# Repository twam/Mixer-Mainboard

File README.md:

Mixer-Mainboard
===

This repository is part of the USB audio mixer project described on https://www.twam.info/general/building-a-custom-usb-audio-mixer.

## License

[![CC BY-SA 4.0][cc-by-sa-shield]][cc-by-sa]

This work is licensed under a [Creative Commons Attribution-NonCommercial-ShareAlike 4.0 International License][cc-by-sa].

[![CC BY-SA 4.0][cc-by-sa-image]][cc-by-sa]

[cc-by-sa]: http://creativecommons.org/licenses/by-nc-sa/4.0/
[cc-by-sa-image]: https://licensebuttons.net/l/by-nc-sa/4.0/88x31.png
[cc-by-sa-shield]: https://img.shields.io/badge/License-CC%20BY--NC--SA%204.0-lightgrey.svg

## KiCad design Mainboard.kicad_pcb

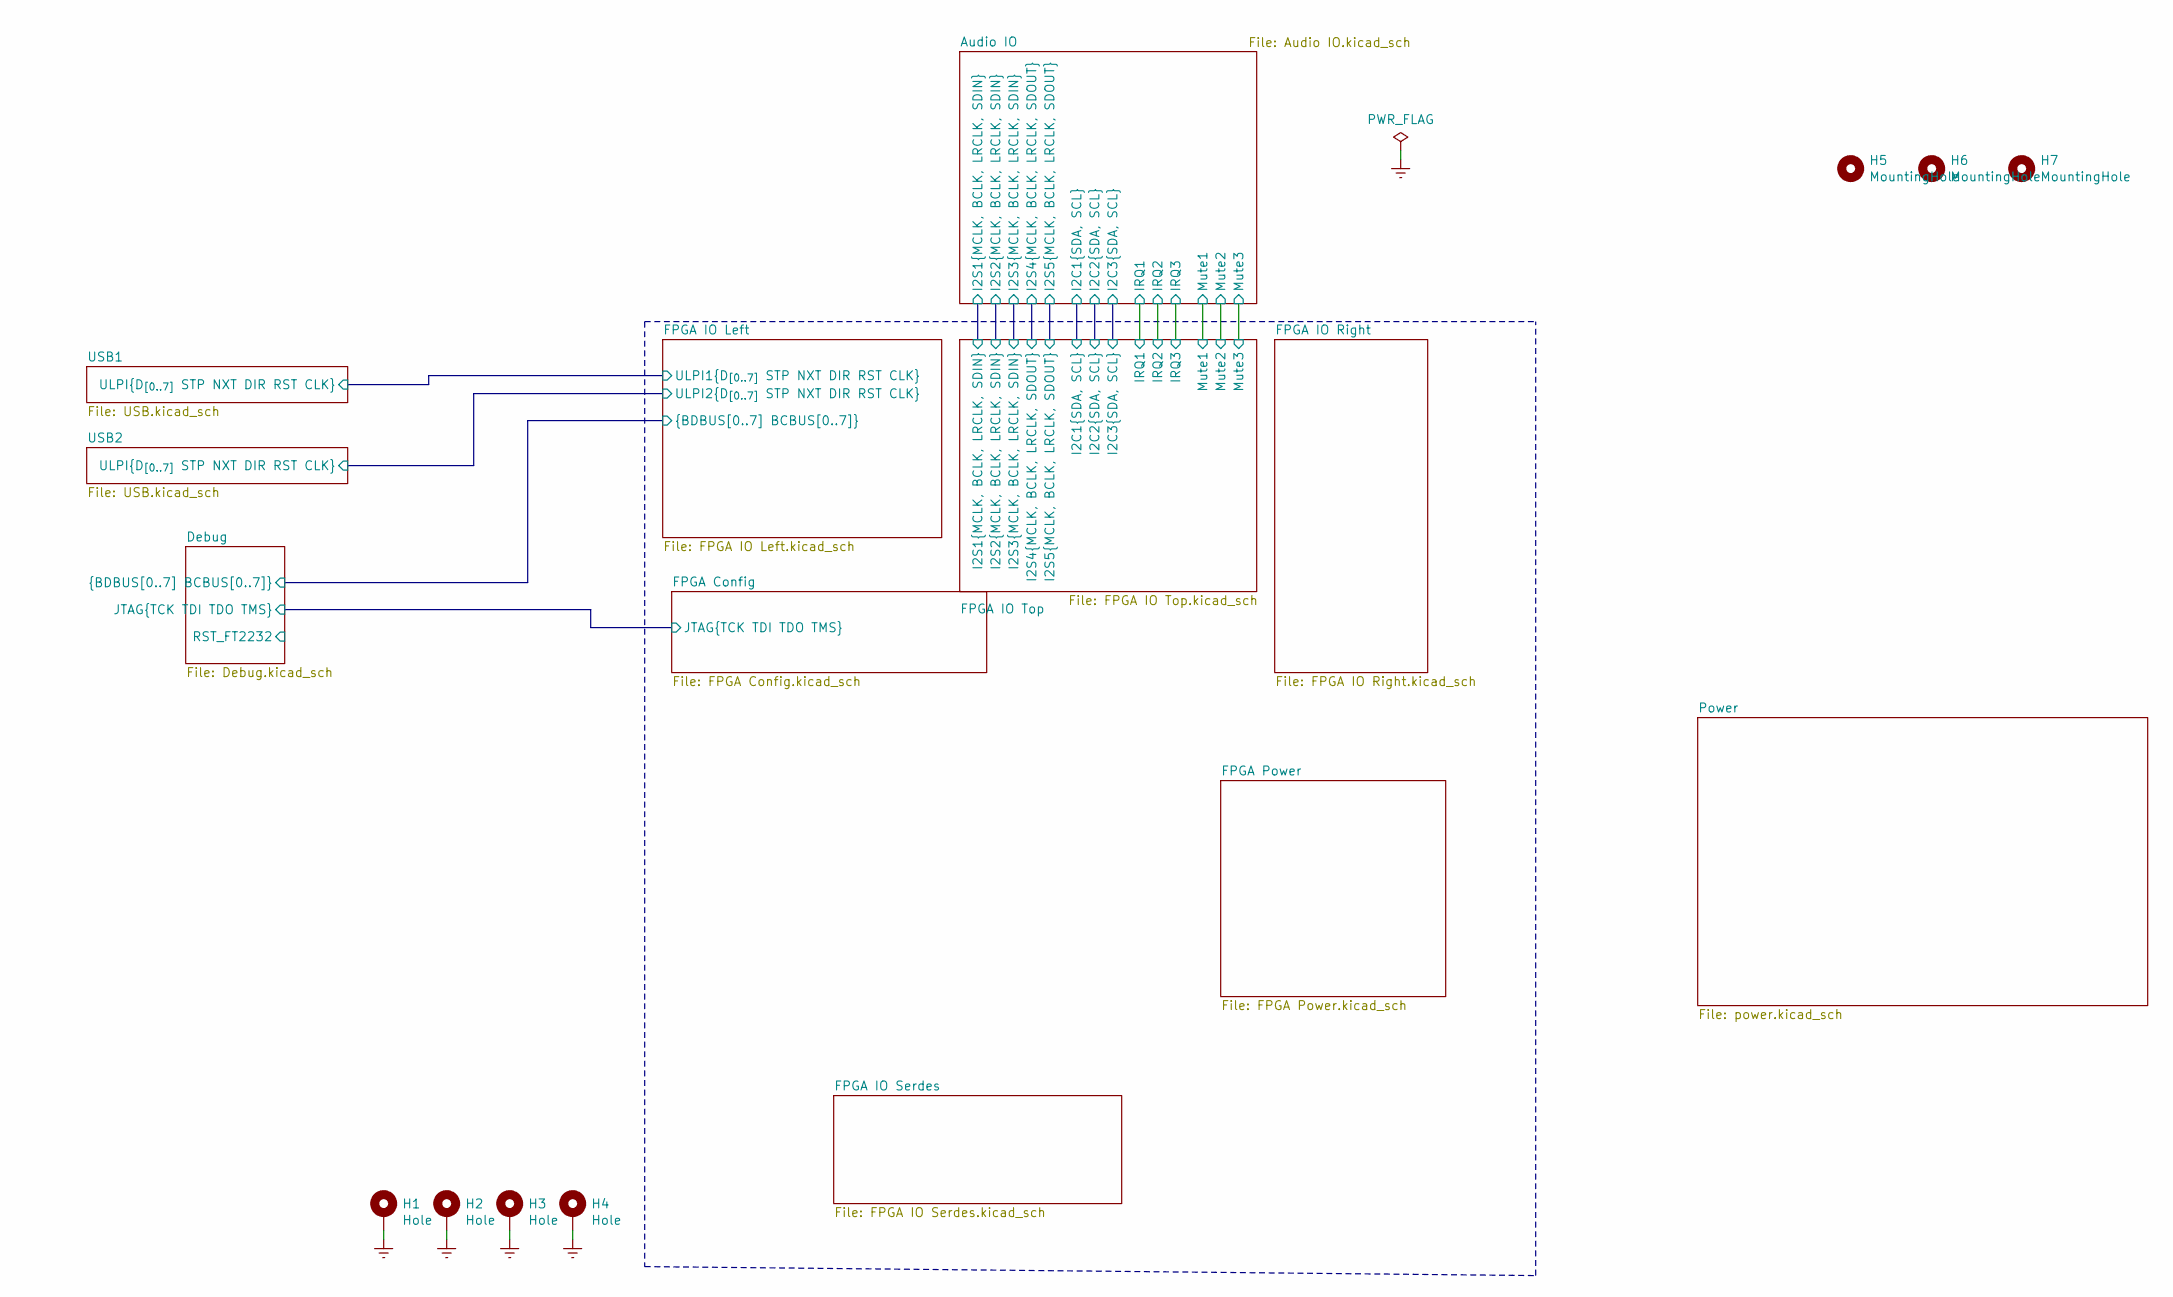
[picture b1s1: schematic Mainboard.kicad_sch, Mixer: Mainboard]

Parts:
H1, H2, H3, H4: Hole; MountingHole_3.2mm_M3_DIN965_Pad
H5, H6, H7: MountingHole; MountingHole_JLCPCB

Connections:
Earth: H1.1, H2.1, H3.1, H4.1; also elsewhere on the board

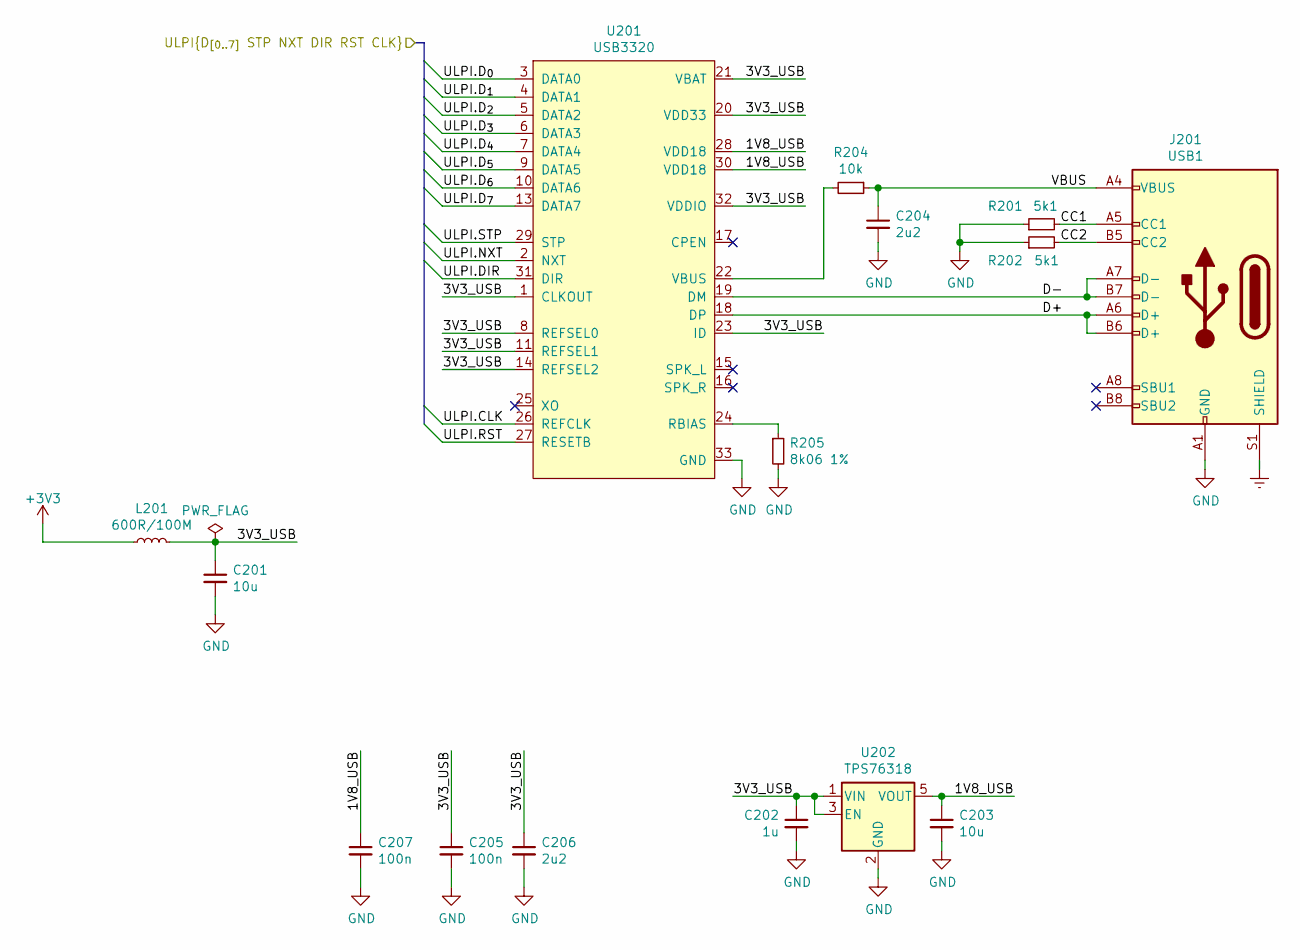
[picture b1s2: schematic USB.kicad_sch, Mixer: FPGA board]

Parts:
C201: 10u; C_0805_2012Metric; LCSC C15850
C202: 1u; C_0603_1608Metric; LCSC C15849
C203: 10u; C_0603_1608Metric; LCSC C19702
C204, C206: 2u2; C_0603_1608Metric; LCSC C23630
C205, C207: 100n; C_0402_1005Metric; LCSC C1525
J201: USB1; USB_C_Receptacle_XKB_TYPE-C-31-M-12; LCSC C165948
L201: 600R/100M; L_0805_2012Metric; LCSC C1017
R201, R202: 5k1; R_0402_1005Metric; LCSC C25905
R204: 10k; R_0402_1005Metric; LCSC C25744
R205: 8k06 1%; R_0603_1608Metric; LCSC C23112
U201: USB3320; QFN-32-1EP_5x5mm_P0.5mm_EP3.3x3.3mm; LCSC C132156
U202: TPS76318; SOT-23-5; LCSC C7099

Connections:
+3V3: L201.1; also elsewhere on the board
/FPGA IO Left/ULPI2.CLK: U201.26 (REFCLK); also elsewhere on the board
/FPGA IO Left/ULPI2.DIR: U201.31 (DIR); also elsewhere on the board
/FPGA IO Left/ULPI2.D_{0}: U201.3 (DATA0); also elsewhere on the board
/FPGA IO Left/ULPI2.D_{1}: U201.4 (DATA1); also elsewhere on the board
/FPGA IO Left/ULPI2.D_{2}: U201.5 (DATA2); also elsewhere on the board
/FPGA IO Left/ULPI2.D_{3}: U201.6 (DATA3); also elsewhere on the board
/FPGA IO Left/ULPI2.D_{4}: U201.7 (DATA4); also elsewhere on the board
/FPGA IO Left/ULPI2.D_{5}: U201.9 (DATA5); also elsewhere on the board
/FPGA IO Left/ULPI2.D_{6}: U201.10 (DATA6); also elsewhere on the board
/FPGA IO Left/ULPI2.D_{7}: U201.13 (DATA7); also elsewhere on the board
/FPGA IO Left/ULPI2.NXT: U201.2 (NXT); also elsewhere on the board
/FPGA IO Left/ULPI2.RST: U201.27 (RESETB); also elsewhere on the board
/FPGA IO Left/ULPI2.STP: U201.29 (STP); also elsewhere on the board
/USB2/1V8_USB: C203.1, C207.1, U201.28 (VDD18), U201.30 (VDD18), U202.5 (VOUT)
/USB2/3V3_USB: C201.1, C202.1, C205.1, C206.1, L201.2, U201.1 (CLKOUT), U201.8 (REFSEL0), U201.11 (REFSEL1), U201.14 (REFSEL2), U201.20 (VDD33), U201.21 (VBAT), U201.23 (ID), U201.32 (VDDIO), U202.1 (VIN), U202.3 (EN)
/USB2/CC1: J201.A5 (CC1), R201.2
/USB2/CC2: J201.B5 (CC2), R202.2
/USB2/D+: J201.A6 (D+), J201.B6 (D+), U201.18 (DP)
/USB2/D-: J201.A7 (D-), J201.B7 (D-), U201.19 (DM)
/USB2/VBUS: C204.1, J201.A4 (VBUS), J201.A9 (VBUS), J201.B4 (VBUS), J201.B9 (VBUS), R204.1
Earth: J201.S1 (SHIELD); also elsewhere on the board
GND: C201.2, C202.2, C203.2, C204.2, C205.2, C206.2, C207.2, J201.A1 (GND), J201.A12 (GND), J201.B1 (GND), J201.B12 (GND), R201.1, R202.1, R205.2, U201.33 (GND), U202.2 (GND); also elsewhere on the board
unnamed: R204.2, U201.22 (VBUS)
unnamed: R205.1, U201.24 (RBIAS)

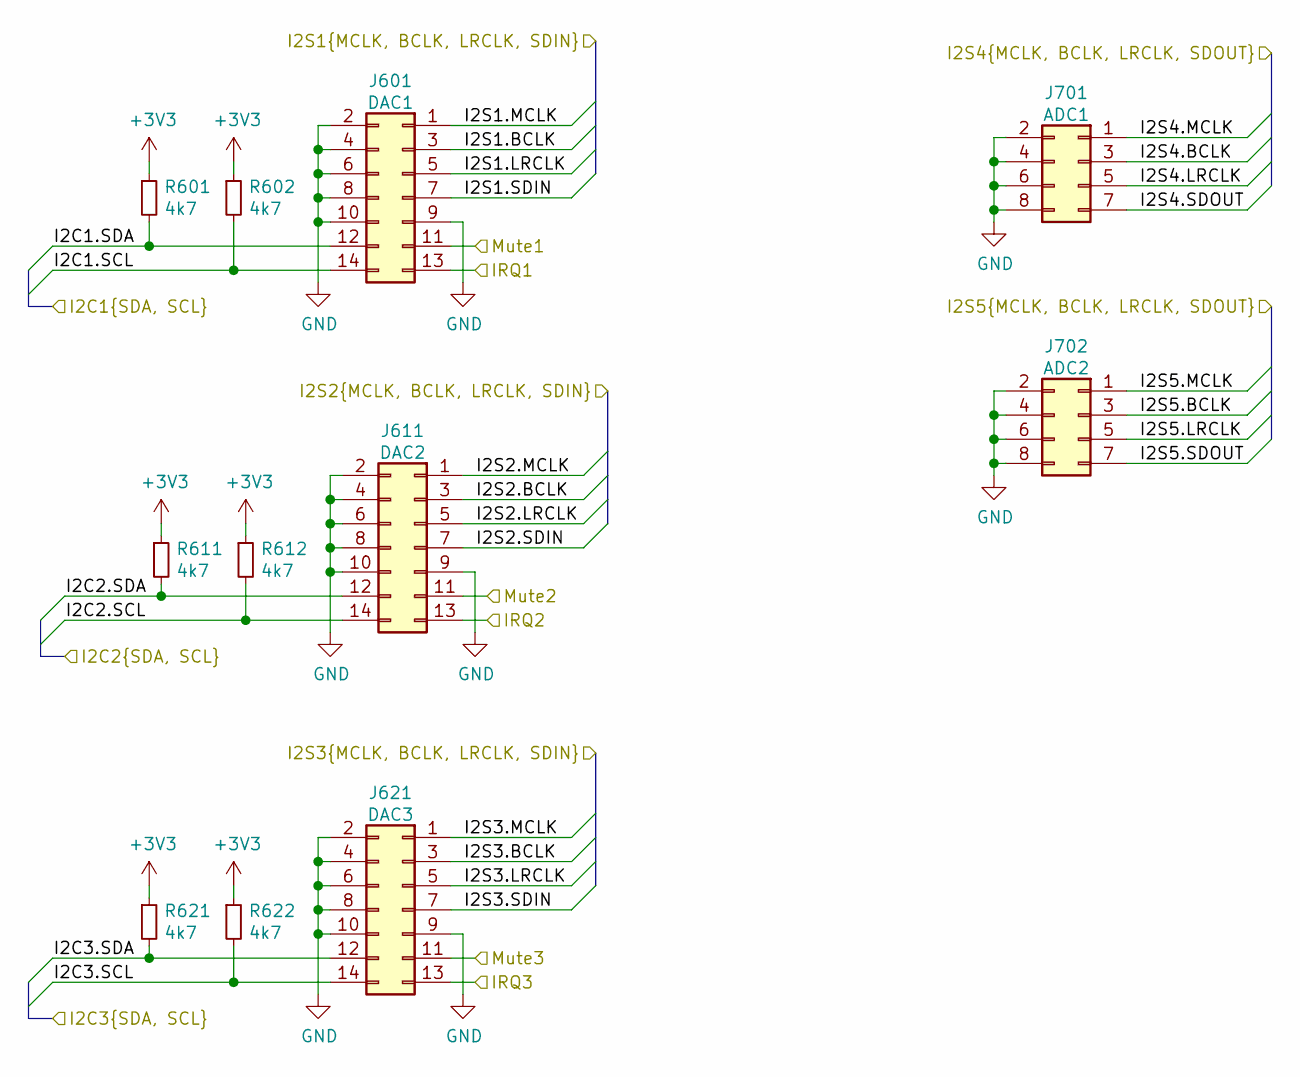
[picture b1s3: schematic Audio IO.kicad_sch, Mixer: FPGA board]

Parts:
J601: DAC1; PinHeader_2x07_P2.54mm_Vertical
J611: DAC2; PinHeader_2x07_P2.54mm_Vertical
J621: DAC3; PinHeader_2x07_P2.54mm_Vertical
J701: ADC1; PinHeader_2x04_P2.54mm_Vertical
J702: ADC2; PinHeader_2x04_P2.54mm_Vertical
R601, R602, R611, R612, R621, R622: 4k7; R_0402_1005Metric; LCSC C25900

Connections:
+3V3: R601.1, R602.1, R611.1, R612.1, R621.1, R622.1; also elsewhere on the board
/Audio IO/I2C1.SCL: J601.14, R602.2; also elsewhere on the board
/Audio IO/I2C1.SDA: J601.12, R601.2; also elsewhere on the board
/Audio IO/I2C2.SCL: J611.14, R612.2; also elsewhere on the board
/Audio IO/I2C2.SDA: J611.12, R611.2; also elsewhere on the board
/Audio IO/I2C3.SCL: J621.14, R622.2; also elsewhere on the board
/Audio IO/I2C3.SDA: J621.12, R621.2; also elsewhere on the board
/Audio IO/I2S1.BCLK: J601.3; also elsewhere on the board
/Audio IO/I2S1.LRCLK: J601.5; also elsewhere on the board
/Audio IO/I2S1.MCLK: J601.1; also elsewhere on the board
/Audio IO/I2S1.SDIN: J601.7; also elsewhere on the board
/Audio IO/I2S2.BCLK: J611.3; also elsewhere on the board
/Audio IO/I2S2.LRCLK: J611.5; also elsewhere on the board
/Audio IO/I2S2.MCLK: J611.1; also elsewhere on the board
/Audio IO/I2S2.SDIN: J611.7; also elsewhere on the board
/Audio IO/I2S3.BCLK: J621.3; also elsewhere on the board
/Audio IO/I2S3.LRCLK: J621.5; also elsewhere on the board
/Audio IO/I2S3.MCLK: J621.1; also elsewhere on the board
/Audio IO/I2S3.SDIN: J621.7; also elsewhere on the board
/Audio IO/I2S4.BCLK: J701.3; also elsewhere on the board
/Audio IO/I2S4.LRCLK: J701.5; also elsewhere on the board
/Audio IO/I2S4.MCLK: J701.1; also elsewhere on the board
/Audio IO/I2S4.SDOUT: J701.7; also elsewhere on the board
/Audio IO/I2S5.BCLK: J702.3; also elsewhere on the board
/Audio IO/I2S5.LRCLK: J702.5; also elsewhere on the board
/Audio IO/I2S5.MCLK: J702.1; also elsewhere on the board
/Audio IO/I2S5.SDOUT: J702.7; also elsewhere on the board
/Audio IO/IRQ1: J601.13; also elsewhere on the board
/Audio IO/IRQ2: J611.13; also elsewhere on the board
/Audio IO/IRQ3: J621.13; also elsewhere on the board
/Audio IO/Mute1: J601.11; also elsewhere on the board
/Audio IO/Mute2: J611.11; also elsewhere on the board
/Audio IO/Mute3: J621.11; also elsewhere on the board
GND: J601.2, J601.4, J601.6, J601.8, J601.9, J601.10, J611.2, J611.4, J611.6, J611.8, J611.9, J611.10, J621.2, J621.4, J621.6, J621.8, J621.9, J621.10, J701.2, J701.4, J701.6, J701.8, J702.2, J702.4, J702.6, J702.8; also elsewhere on the board

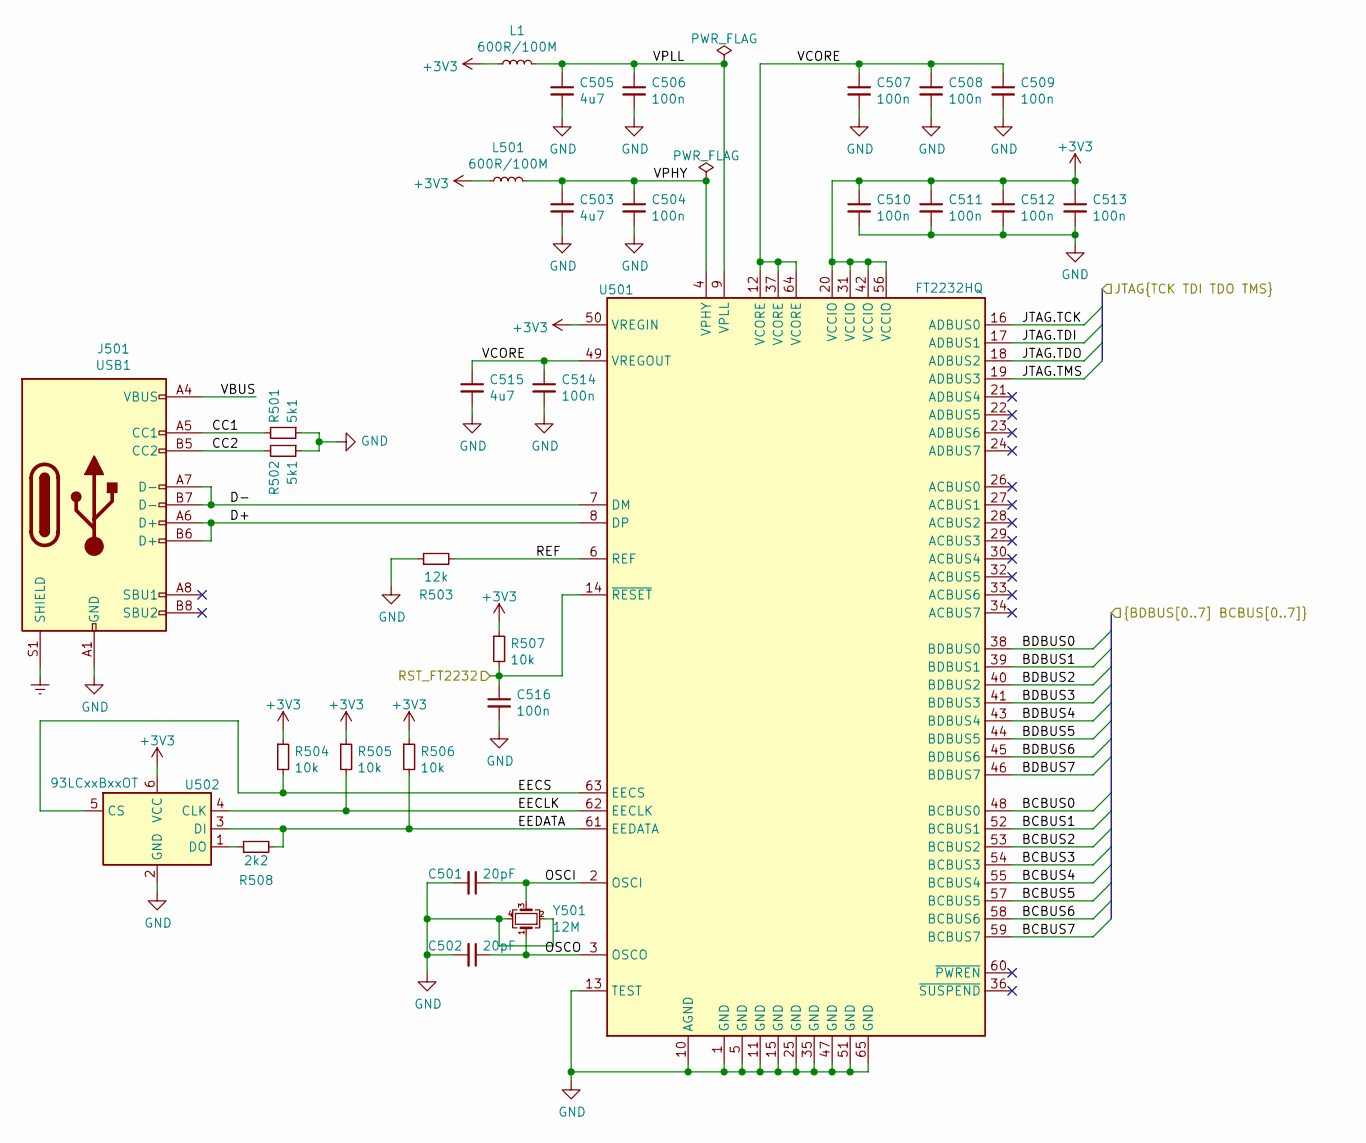
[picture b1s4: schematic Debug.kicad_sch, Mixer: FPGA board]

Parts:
C501, C502: 20pF; C_0402_1005Metric; LCSC C1554
C503, C505, C515: 4u7; C_0603_1608Metric; LCSC C19666
C504, C506, C507, C508, C509, C510, C511, C512, C513, C514, C516: 100n; C_0402_1005Metric; LCSC C1525
J501: USB1; USB_C_Receptacle_XKB_TYPE-C-31-M-12; LCSC C165948
L1, L501: 600R/100M; L_0805_2012Metric; LCSC C1017
R501, R502: 5k1; R_0402_1005Metric; LCSC C25905
R503: 12k; R_0402_1005Metric; LCSC C25752
R504, R505, R506, R507: 10k; R_0402_1005Metric; LCSC C25744
R508: 2k2; R_0402_1005Metric; LCSC C25879
U501: FT2232HQ; QFN-64-1EP_9x9mm_P0.5mm_EP4.35x4.35mm; LCSC C193662
U502: 93LCxxBxxOT; SOT-23-6; LCSC C190271
Y501: 12M; Crystal_SMD_3225-4Pin_3.2x2.5mm; LCSC C9002

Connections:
+3V3: C510.1, C511.1, C512.1, C513.1, L1.1, L501.1, R504.1, R505.1, R506.1, R507.2, U501.20 (VCCIO), U501.31 (VCCIO), U501.42 (VCCIO), U501.50 (VREGIN), U501.56 (VCCIO), U502.6 (VCC); also elsewhere on the board
/Debug/BCBUS0: U501.48 (BCBUS0); also elsewhere on the board
/Debug/BCBUS1: U501.52 (BCBUS1); also elsewhere on the board
/Debug/BCBUS2: U501.53 (BCBUS2); also elsewhere on the board
/Debug/BCBUS3: U501.54 (BCBUS3); also elsewhere on the board
/Debug/BCBUS4: U501.55 (BCBUS4); also elsewhere on the board
/Debug/BCBUS5: U501.57 (BCBUS5); also elsewhere on the board
/Debug/BCBUS6: U501.58 (BCBUS6); also elsewhere on the board
/Debug/BCBUS7: U501.59 (BCBUS7); also elsewhere on the board
/Debug/BDBUS0: U501.38 (BDBUS0); also elsewhere on the board
/Debug/BDBUS1: U501.39 (BDBUS1); also elsewhere on the board
/Debug/BDBUS2: U501.40 (BDBUS2); also elsewhere on the board
/Debug/BDBUS3: U501.41 (BDBUS3); also elsewhere on the board
/Debug/BDBUS4: U501.43 (BDBUS4); also elsewhere on the board
/Debug/BDBUS5: U501.44 (BDBUS5); also elsewhere on the board
/Debug/BDBUS6: U501.45 (BDBUS6); also elsewhere on the board
/Debug/BDBUS7: U501.46 (BDBUS7); also elsewhere on the board
/Debug/CC1: J501.A5 (CC1), R501.2
/Debug/CC2: J501.B5 (CC2), R502.2
/Debug/D+: J501.A6 (D+), J501.B6 (D+), U501.8 (DP)
/Debug/D-: J501.A7 (D-), J501.B7 (D-), U501.7 (DM)
/Debug/EECLK: R505.2, U501.62 (EECLK), U502.4 (CLK)
/Debug/EECS: R504.2, U501.63 (EECS), U502.5 (CS)
/Debug/EEDATA: R506.2, R508.2, U501.61 (EEDATA), U502.3 (DI)
/Debug/JTAG.TCK: U501.16 (ADBUS0); also elsewhere on the board
/Debug/JTAG.TDI: U501.17 (ADBUS1); also elsewhere on the board
/Debug/JTAG.TDO: U501.18 (ADBUS2); also elsewhere on the board
/Debug/JTAG.TMS: U501.19 (ADBUS3); also elsewhere on the board
/Debug/OSCI: C501.1, U501.2 (OSCI), Y501.3
/Debug/OSCO: C502.1, U501.3 (OSCO), Y501.1
/Debug/REF: R503.2, U501.6 (REF)
/Debug/RST_FT2232: C516.1, R507.1, U501.14 (~RESET)
/Debug/VBUS: J501.A4 (VBUS), J501.A9 (VBUS), J501.B4 (VBUS), J501.B9 (VBUS)
/Debug/VCORE: C507.1, C508.1, C509.1, C514.1, C515.1, U501.12 (VCORE), U501.37 (VCORE), U501.49 (VREGOUT), U501.64 (VCORE)
/Debug/VPHY: C503.1, C504.1, L501.2, U501.4 (VPHY)
/Debug/VPLL: C505.1, C506.1, L1.2, U501.9 (VPLL)
Earth: J501.S1 (SHIELD); also elsewhere on the board
GND: C501.2, C502.2, C503.2, C504.2, C505.2, C506.2, C507.2, C508.2, C509.2, C510.2, C511.2, C512.2, C513.2, C514.2, C515.2, C516.2, J501.A1 (GND), J501.A12 (GND), J501.B1 (GND), J501.B12 (GND), R501.1, R502.1, R503.1, U501.1 (GND), U501.5 (GND), U501.10 (AGND), U501.11 (GND), U501.13 (TEST), U501.15 (GND), U501.25 (GND), U501.35 (GND), U501.47 (GND), U501.51 (GND), U501.65 (GND), U502.2 (GND), Y501.2, Y501.4; also elsewhere on the board
unnamed: R508.1, U502.1 (DO)

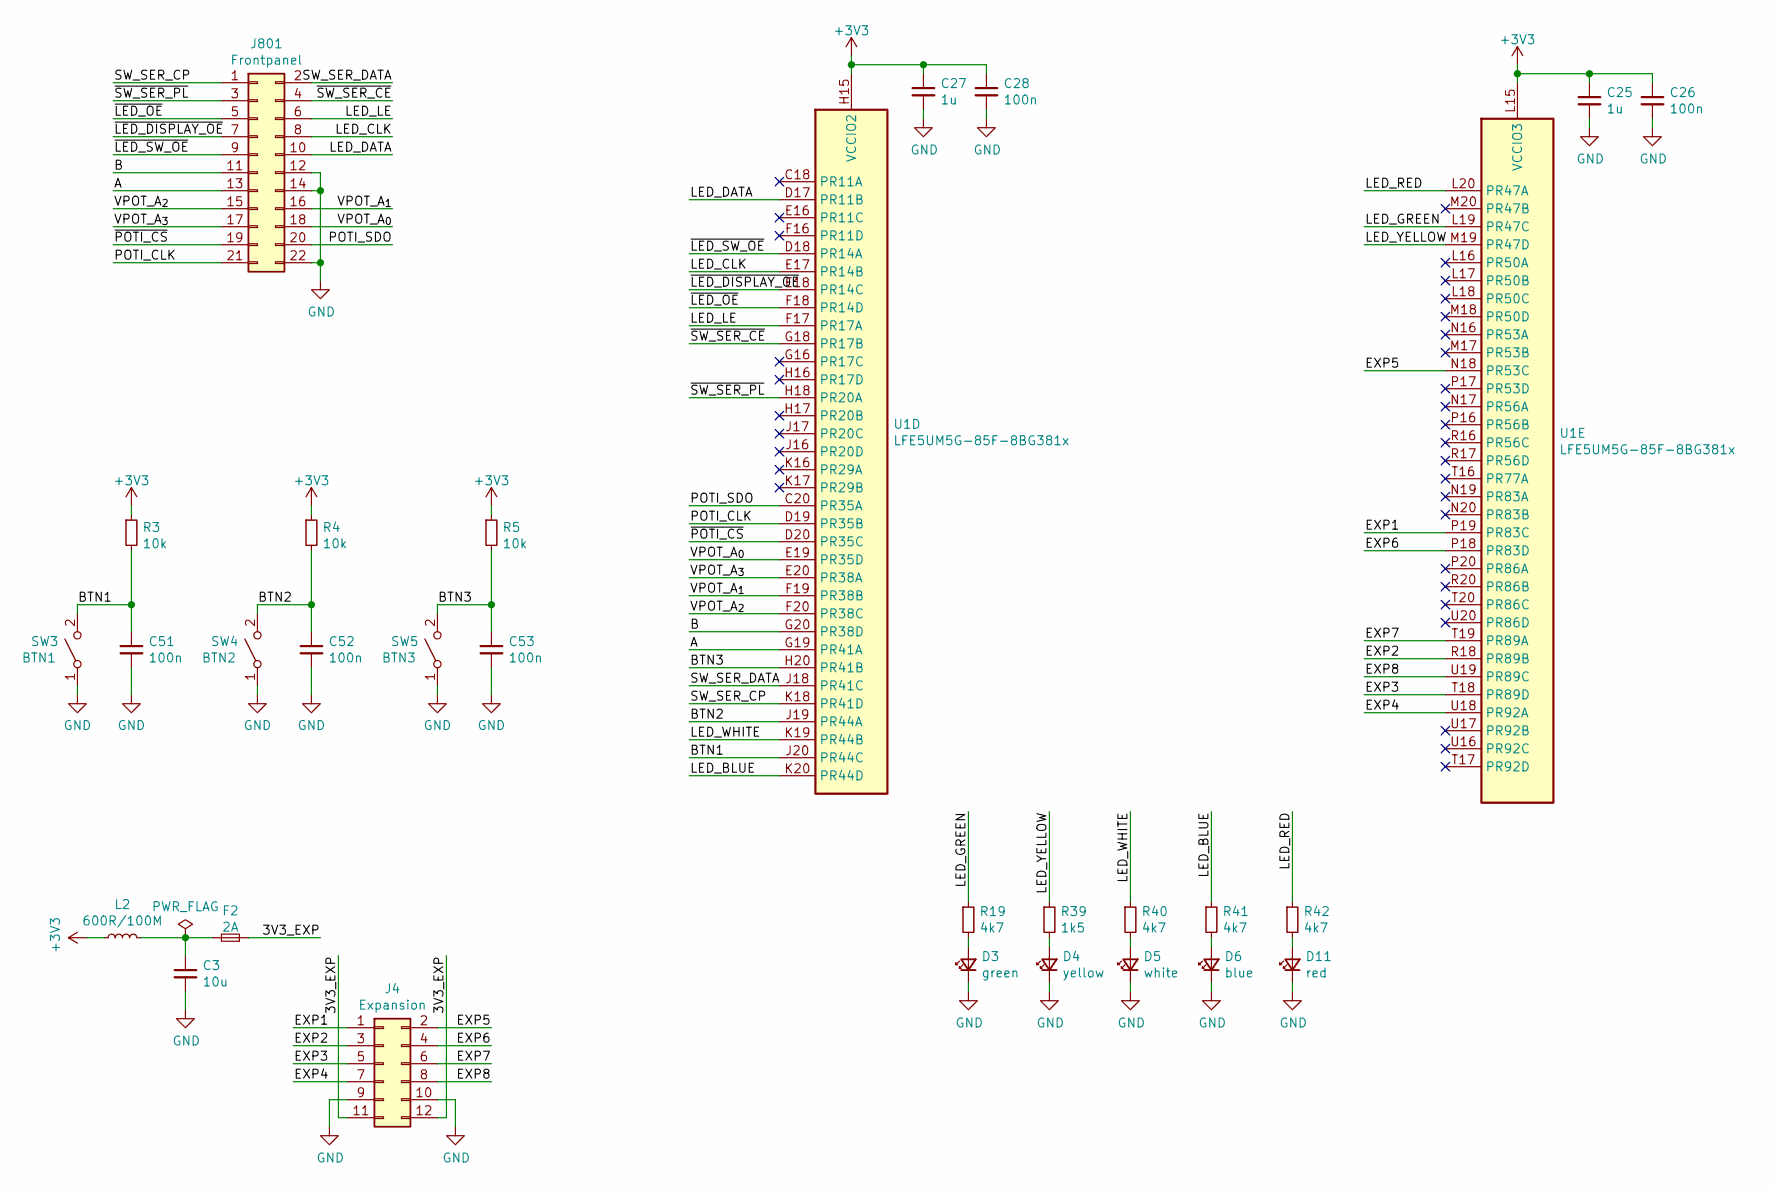
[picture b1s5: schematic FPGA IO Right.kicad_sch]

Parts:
C3: 10u; C_0805_2012Metric; LCSC C15850
C25, C27: 1u; C_0402_1005Metric; LCSC C52923
C26, C28, C51, C52, C53: 100n; C_0402_1005Metric; LCSC C1525
D3: green; LED_0603_1608Metric; LCSC C72043
D4: yellow; LED_0603_1608Metric; LCSC C72038
D5: white; LED_0603_1608Metric; LCSC C2290
D6: blue; LED_0603_1608Metric; LCSC C72041
D11: red; LED_0603_1608Metric; LCSC C2286
F2: 2A; Fuse_0603_1608Metric_Pad1.05x0.95mm_HandSolder; LCSC C187605
J4: Expansion; PinHeader_2x06_P2.54mm_Vertical
J801: Frontpanel; PinHeader_2x11_P2.54mm_Vertical
L2: 600R/100M; L_0805_2012Metric; LCSC C1017
R3, R4, R5: 10k; R_0402_1005Metric; LCSC C25744
R19, R40, R41, R42: 4k7; R_0402_1005Metric; LCSC C25900
R39: 1k5; R_0402_1005Metric; LCSC C25867
SW3: BTN1; SW_SPST_B3U-1000P; LCSC C231329
SW4: BTN2; SW_SPST_B3U-1000P; LCSC C231329
SW5: BTN3; SW_SPST_B3U-1000P; LCSC C231329
U1: LFE5UM5G-85F-8BG381x; Lattice_caBGA-381_17.0x17.0mm_Layout20x20_P0.8mm_Ball0.4mm_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

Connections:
+3V3: C25.1, C26.1, C27.1, C28.1, L2.1, R3.1, R4.1, R5.1, U1.H14 (VCCIO2), U1.H15 (VCCIO2), U1.J15 (VCCIO2), U1.L14 (VCCIO3), U1.L15 (VCCIO3), U1.M15 (VCCIO3); also elsewhere on the board
/FPGA IO Right/3V3_EXP: F2.1, J4.11, J4.12
/FPGA IO Right/A: J801.13, U1.G19 (PR41A)
/FPGA IO Right/B: J801.11, U1.G20 (PR38D)
/FPGA IO Right/BTN1: C51.1, R3.2, SW3.2 (B), U1.J20 (PR44C)
/FPGA IO Right/BTN2: C52.1, R4.2, SW4.2 (B), U1.J19 (PR44A)
/FPGA IO Right/BTN3: C53.1, R5.2, SW5.2 (B), U1.H20 (PR41B)
/FPGA IO Right/EXP1: J4.1, U1.P19 (PR83C)
/FPGA IO Right/EXP2: J4.3, U1.R18 (PR89B)
/FPGA IO Right/EXP3: J4.5, U1.T18 (PR89D)
/FPGA IO Right/EXP4: J4.7, U1.U18 (PR92A)
/FPGA IO Right/EXP5: J4.2, U1.N18 (PR53C)
/FPGA IO Right/EXP6: J4.4, U1.P18 (PR83D)
/FPGA IO Right/EXP7: J4.6, U1.T19 (PR89A)
/FPGA IO Right/EXP8: J4.8, U1.U19 (PR89C)
/FPGA IO Right/LED_BLUE: R41.1, U1.K20 (PR44D)
/FPGA IO Right/LED_CLK: J801.8, U1.E17 (PR14B)
/FPGA IO Right/LED_DATA: J801.10, U1.D17 (PR11B)
/FPGA IO Right/LED_GREEN: R19.1, U1.L19 (PR47C)
/FPGA IO Right/LED_LE: J801.6, U1.F17 (PR17A)
/FPGA IO Right/LED_RED: R42.1, U1.L20 (PR47A)
/FPGA IO Right/LED_WHITE: R40.1, U1.K19 (PR44B)
/FPGA IO Right/LED_YELLOW: R39.1, U1.M19 (PR47D)
/FPGA IO Right/POTI_CLK: J801.21, U1.D19 (PR35B)
/FPGA IO Right/POTI_SDO: J801.20, U1.C20 (PR35A)
/FPGA IO Right/SW_SER_CP: J801.1, U1.K18 (PR41D)
/FPGA IO Right/SW_SER_DATA: J801.2, U1.J18 (PR41C)
/FPGA IO Right/VPOT_A_{0}: J801.18, U1.E19 (PR35D)
/FPGA IO Right/VPOT_A_{1}: J801.16, U1.F19 (PR38B)
/FPGA IO Right/VPOT_A_{2}: J801.15, U1.F20 (PR38C)
/FPGA IO Right/VPOT_A_{3}: J801.17, U1.E20 (PR38A)
/FPGA IO Right/~LED_DISPLAY_OE: J801.7, U1.E18 (PR14C)
/FPGA IO Right/~LED_OE: J801.5, U1.F18 (PR14D)
/FPGA IO Right/~LED_SW_OE: J801.9, U1.D18 (PR14A)
/FPGA IO Right/~POTI_CS: J801.19, U1.D20 (PR35C)
/FPGA IO Right/~SW_SER_CE: J801.4, U1.G18 (PR17B)
/FPGA IO Right/~SW_SER_PL: J801.3, U1.H18 (PR20A)
GND: C3.2, C25.2, C26.2, C27.2, C28.2, C51.2, C52.2, C53.2, D3.1 (K), D4.1 (K), D5.1 (K), D6.1 (K), D11.1 (K), J4.9, J4.10, J801.12, J801.14, J801.22, SW3.1 (A), SW4.1 (A), SW5.1 (A); also elsewhere on the board
unnamed: C3.1, F2.2, L2.2
unnamed: D3.2 (A), R19.2
unnamed: D4.2 (A), R39.2
unnamed: D5.2 (A), R40.2
unnamed: D6.2 (A), R41.2
unnamed: D11.2 (A), R42.2

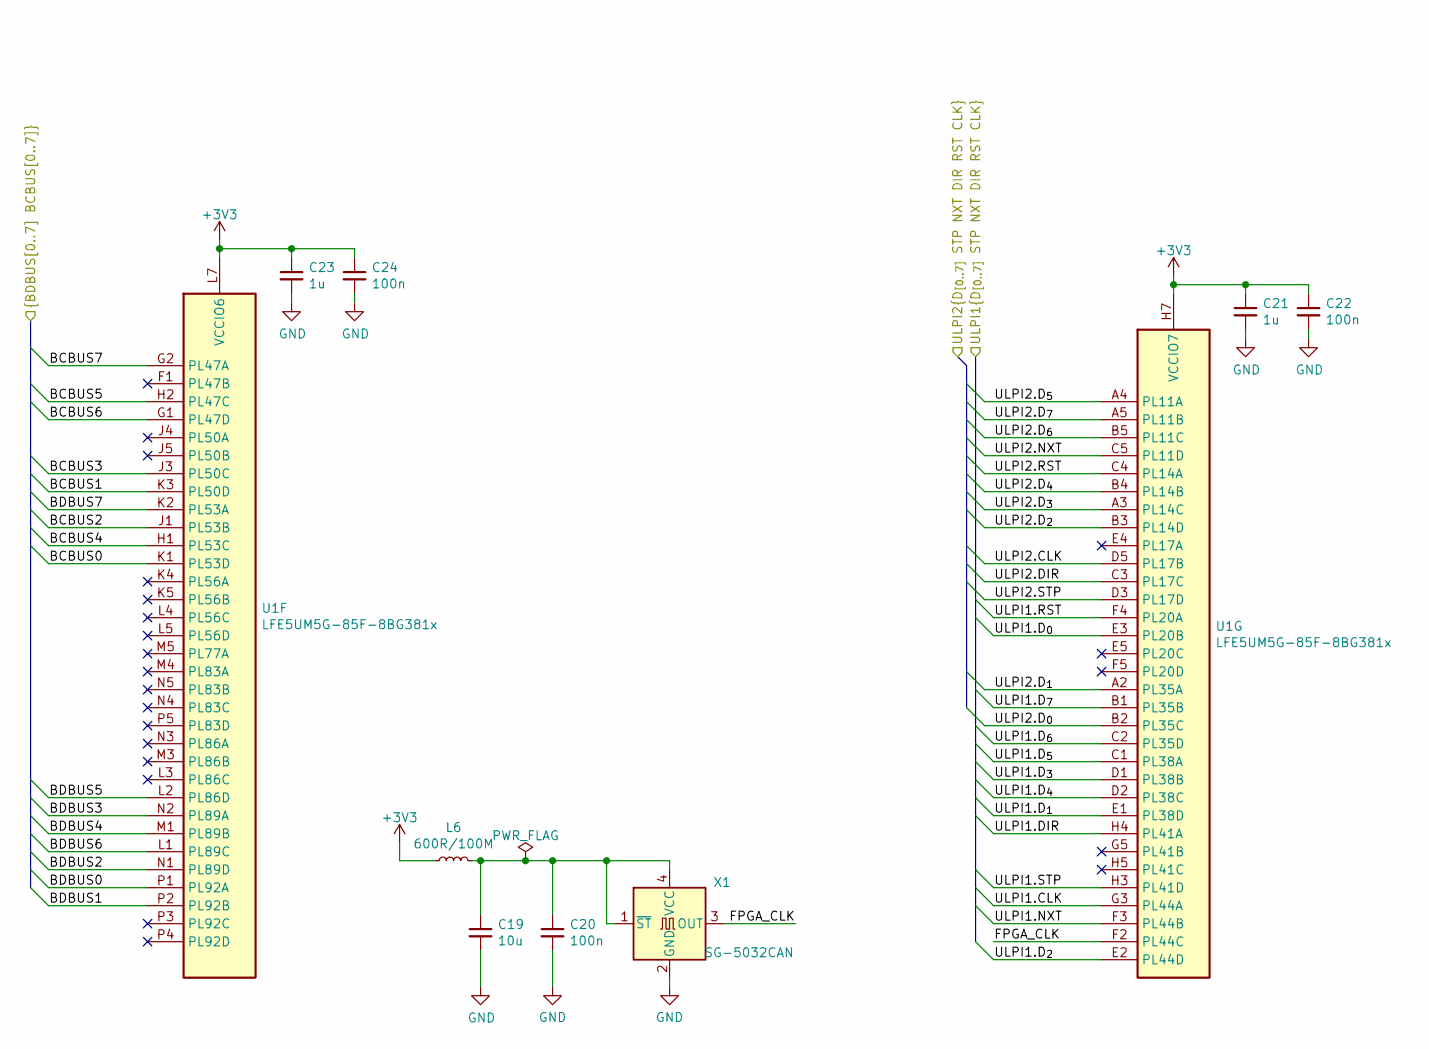
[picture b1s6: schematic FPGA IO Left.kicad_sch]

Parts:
C19: 10u; C_0805_2012Metric; LCSC C15850
C20, C22, C24: 100n; C_0402_1005Metric; LCSC C1525
C21, C23: 1u; C_0402_1005Metric; LCSC C52923
L6: 600R/100M; L_0805_2012Metric; LCSC C1017
U1: LFE5UM5G-85F-8BG381x; Lattice_caBGA-381_17.0x17.0mm_Layout20x20_P0.8mm_Ball0.4mm_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
X1: SG-5032CAN; Oscillator_SMD_SeikoEpson_SG8002LB-4Pin_5.0x3.2mm; LCSC C37076

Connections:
+3V3: C21.1, C22.1, C23.1, C24.1, L6.1, U1.H6 (VCCIO7), U1.H7 (VCCIO7), U1.J6 (VCCIO7), U1.L6 (VCCIO6), U1.L7 (VCCIO6), U1.M6 (VCCIO6); also elsewhere on the board
/Debug/BCBUS0: U1.K1 (PL53D); also elsewhere on the board
/Debug/BCBUS1: U1.K3 (PL50D); also elsewhere on the board
/Debug/BCBUS2: U1.J1 (PL53B); also elsewhere on the board
/Debug/BCBUS3: U1.J3 (PL50C); also elsewhere on the board
/Debug/BCBUS4: U1.H1 (PL53C); also elsewhere on the board
/Debug/BCBUS5: U1.H2 (PL47C); also elsewhere on the board
/Debug/BCBUS6: U1.G1 (PL47D); also elsewhere on the board
/Debug/BCBUS7: U1.G2 (PL47A); also elsewhere on the board
/Debug/BDBUS0: U1.P1 (PL92A); also elsewhere on the board
/Debug/BDBUS1: U1.P2 (PL92B); also elsewhere on the board
/Debug/BDBUS2: U1.N1 (PL89D); also elsewhere on the board
/Debug/BDBUS3: U1.N2 (PL89A); also elsewhere on the board
/Debug/BDBUS4: U1.M1 (PL89B); also elsewhere on the board
/Debug/BDBUS5: U1.L2 (PL86D); also elsewhere on the board
/Debug/BDBUS6: U1.L1 (PL89C); also elsewhere on the board
/Debug/BDBUS7: U1.K2 (PL53A); also elsewhere on the board
/FPGA IO Left/FPGA_CLK: U1.F2 (PL44C), X1.3 (OUT)
/FPGA IO Left/ULPI1.CLK: U1.G3 (PL44A); also elsewhere on the board
/FPGA IO Left/ULPI1.DIR: U1.H4 (PL41A); also elsewhere on the board
/FPGA IO Left/ULPI1.D_{0}: U1.E3 (PL20B); also elsewhere on the board
/FPGA IO Left/ULPI1.D_{1}: U1.E1 (PL38D); also elsewhere on the board
/FPGA IO Left/ULPI1.D_{2}: U1.E2 (PL44D); also elsewhere on the board
/FPGA IO Left/ULPI1.D_{3}: U1.D1 (PL38B); also elsewhere on the board
/FPGA IO Left/ULPI1.D_{4}: U1.D2 (PL38C); also elsewhere on the board
/FPGA IO Left/ULPI1.D_{5}: U1.C1 (PL38A); also elsewhere on the board
/FPGA IO Left/ULPI1.D_{6}: U1.C2 (PL35D); also elsewhere on the board
/FPGA IO Left/ULPI1.D_{7}: U1.B1 (PL35B); also elsewhere on the board
/FPGA IO Left/ULPI1.NXT: U1.F3 (PL44B); also elsewhere on the board
/FPGA IO Left/ULPI1.RST: U1.F4 (PL20A); also elsewhere on the board
/FPGA IO Left/ULPI1.STP: U1.H3 (PL41D); also elsewhere on the board
/FPGA IO Left/ULPI2.CLK: U1.D5 (PL17B); also elsewhere on the board
/FPGA IO Left/ULPI2.DIR: U1.C3 (PL17C); also elsewhere on the board
/FPGA IO Left/ULPI2.D_{0}: U1.B2 (PL35C); also elsewhere on the board
/FPGA IO Left/ULPI2.D_{1}: U1.A2 (PL35A); also elsewhere on the board
/FPGA IO Left/ULPI2.D_{2}: U1.B3 (PL14D); also elsewhere on the board
/FPGA IO Left/ULPI2.D_{3}: U1.A3 (PL14C); also elsewhere on the board
/FPGA IO Left/ULPI2.D_{4}: U1.B4 (PL14B); also elsewhere on the board
/FPGA IO Left/ULPI2.D_{5}: U1.A4 (PL11A); also elsewhere on the board
/FPGA IO Left/ULPI2.D_{6}: U1.B5 (PL11C); also elsewhere on the board
/FPGA IO Left/ULPI2.D_{7}: U1.A5 (PL11B); also elsewhere on the board
/FPGA IO Left/ULPI2.NXT: U1.C5 (PL11D); also elsewhere on the board
/FPGA IO Left/ULPI2.RST: U1.C4 (PL14A); also elsewhere on the board
/FPGA IO Left/ULPI2.STP: U1.D3 (PL17D); also elsewhere on the board
GND: C19.2, C20.2, C21.2, C22.2, C23.2, C24.2, X1.2 (GND); also elsewhere on the board
unnamed: C19.1, C20.1, L6.2, X1.1 (~ST), X1.4 (VCC)
